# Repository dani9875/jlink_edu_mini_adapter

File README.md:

# Jlink edu mini adapter

# How to
Coming soon...

## Release notes

### Version: v1.0
Changelog:
- Initial version to convert 1.27 mm 2x5P JLINK EDU MINI IDC to 2.54 mm 2x5P (to plug of nails connector end) with VBUS support

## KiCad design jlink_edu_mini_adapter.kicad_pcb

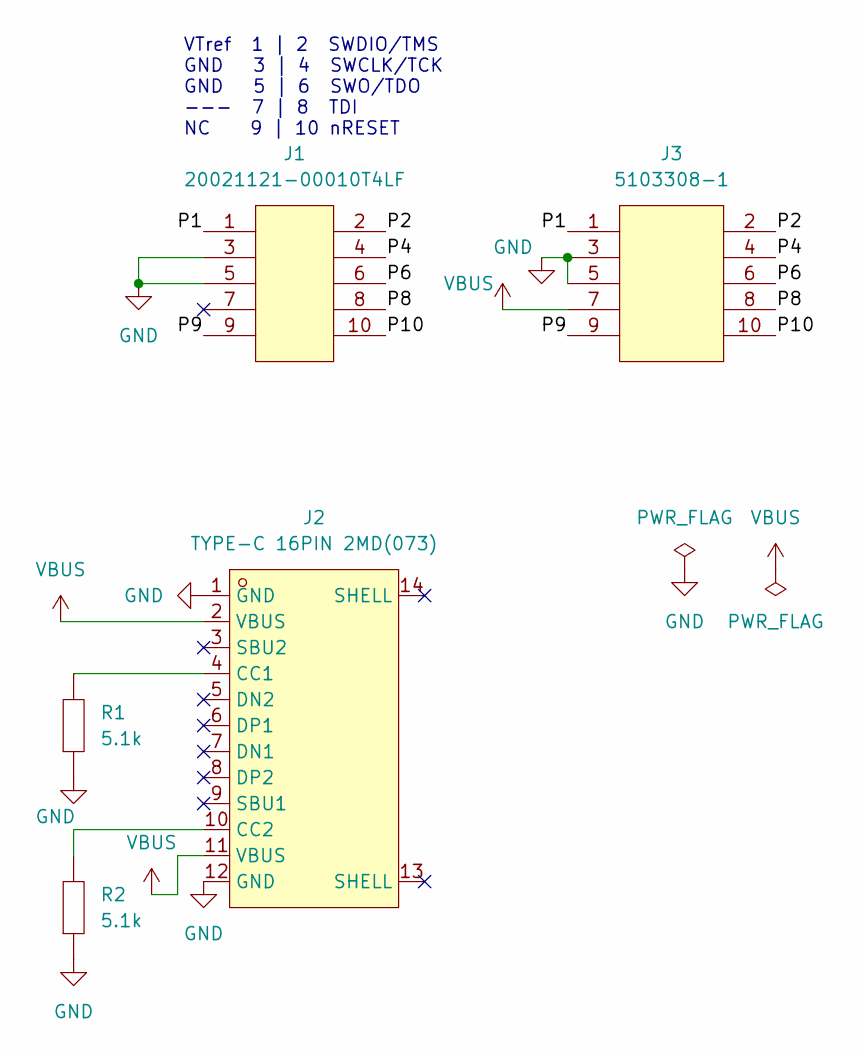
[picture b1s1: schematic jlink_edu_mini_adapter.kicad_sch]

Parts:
J1: 20021121-00010T4LF; [10P_2X5_IDC_1_27MM_MALE]Amphenol ICC 20021121-00010T4LF; LCSC Part C598540
J2: TYPE-C 16PIN 2MD(073); [USB_C_16P_RA_FEMALE]SHOU HAN TYPE-C 16PIN 2MD(073); LCSC Part C2765186
J3: 5103308-1; [10P_2X5_IDC_MALE]TE Connectivity 5103308-1; LCSC Part C86466
R1, R2: 0805W8F5101T5E; [RES_SMD_0805_2012Metric]; LCSC Part C27834

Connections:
/P1: J1.1, J3.1
/P2: J1.2, J3.2
/P4: J1.4, J3.4
/P6: J1.6, J3.6
/P8: J1.8, J3.8
/P9: J1.9, J3.9
/P10: J1.10, J3.10
GND: J1.3, J1.5, J2.1 (GND), J2.12 (GND), J3.3, J3.5, R1.1, R2.1
unnamed: J2.4 (CC1), R1.2
unnamed: J2.10 (CC2), R2.2
VBUS: J2.2 (VBUS), J2.11 (VBUS), J3.7

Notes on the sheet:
VTref 1 | 2 SWDIO/TMS GND 3 | 4 SWCLK/TCK GND 5 | 6 SWO/TDO --- 7 | 8 TDI NC 9 | 10 nRESET

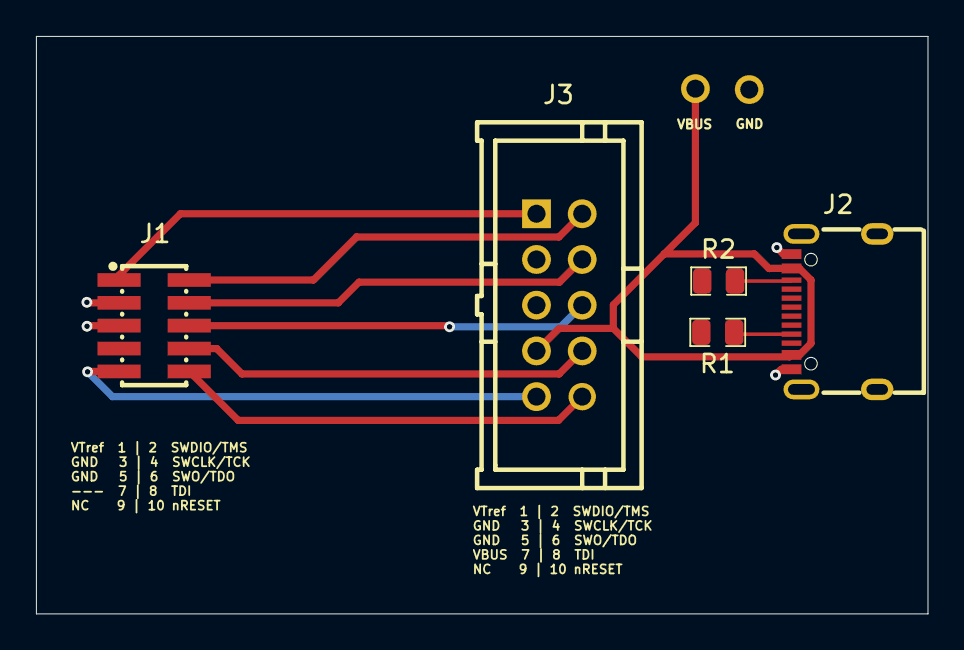
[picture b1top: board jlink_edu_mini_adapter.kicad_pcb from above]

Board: 2 copper layers, 49.5 x 32.1 mm, 5 parts (0 on the bottom side), 11 nets.

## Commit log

2024-07-28 Kicad library added
2025-03-13 Update...
